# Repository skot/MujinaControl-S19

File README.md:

# MujinaControl-S19

An open-hardware Antminer S19 controlboard built around the Rockchip RV1106G2, for [Mujina](https://mujina.org) mining firmware. It keeps the bitcrane v3.1 form factor, outline, mounting holes and miner connectors, and replaces bitcrane's RP2040 with a Linux-capable SoC, Ethernet and local storage.

**Status (2026-11-14):** schematic complete, PCB placed and fully routed on six layers, with on-board WiFi. ERC 0; DRC 0 violations, 0 unconnected items, 0 schematic-parity issues. Every purchased part has a fab (LCSC) part number. Reviewed against the fab's manufacturing limits on 2026-11-14. **Not built or tested.** Read "Before ordering" below first.

Open `MujinaControl-S19.kicad_pro` with **KiCad 10.99 or later**. The files use a newer format than KiCad 10.0 can read.

## Hardware

- **SoC:** RV1106G2 with 128 MB in-package DDR3L, 24 MHz crystal and RTC crystal.
- **Storage:** W25N02KVZEIR 2 Gbit (256 MB) SPI NAND on the quad-SPI bus, following the Luckfox Pico Pro/Max, plus a microSD socket. A bootable NAND takes precedence over microSD.
- **Network and USB:** 100BASE-TX through the SoC's internal PHY and an integrated MagJack with the latch tab on top (HanRun HR915340A). USB-C device port for recovery and console; VBUS is detection-only, so **12 V must be present for USB recovery**.
- **Power:** 12 V from J1's 6-pin input (pins 1–3 positive, 4–6 ground) through reverse-polarity P-MOSFET Q1 (SiSS27DN-T1-GE3) and an SMBJ15A TVS. There is no controller fuse. Six TPS62933 bucks: 12 V → 5 V system (2 A budget), then sequenced 0.9 V core, 0.9 V CPU, 1.35 V DDR, 1.8 V and 3.3 V. Five TPS3808 supervisors (trip at about 90 % of each rail) qualify the sequence and hold reset.
- **Hashboards:** three ports, each with its own hardware UART, sharing one hashboard I²C bus; BCB100-style I²C/UART pull-ups and plug-detect pull-downs, and a TPS22919 switched 3.3 V supply per port, enabled directly by SoC GPIOs.
- **Fans:** four independent channels, PWM and tach, each sized for 3 A; the input stage carries all four fans plus the board. Each channel has both a 1×4 2.54 mm and a 2×2 4.2 mm footprint. The fab fits neither: solder in the one the machine needs. Two 100 µF bulk capacitors on the fan rail.
- **WiFi:** AMPAK AP6212 2.4 GHz 802.11 b/g/n module on 4-bit SDIO, with its own 26 MHz crystal and a U.FL connector (J19) for an external antenna; there is no on-board antenna. Bluetooth is not wired. See `docs/onboard-wifi.md`.
- **PSU and accessories:** PSU I²C and enable, 2×7 accessory header J15 (display I²C, six GPIO, 5 V / 3.3 V / 1.8 V; not fitted by the fab), console UART on J16 (pin 1 TX, 2 GND, 3 RX, 3.3 V), RESET and BOOT (maskrom) right-angle buttons beside the Ethernet jack.

J1–J14 keep bitcrane's pin assignments. For firmware, `docs/firmware-pins.md` lists every SoC pin, its function, polarity and voltage, with device-tree starting points. The history of the pin allocation is in `docs/pin-allocation.md`.

## Schematic

Eleven sheets: system overview, SoC interfaces, sequenced regulators, power qualification, SoC supply and bypass, boot storage and clocks, Ethernet and USB, hashboard interfaces, fan interfaces, input power and service, on-board WiFi. Cross-sheet signals use global labels; resistors use US-style symbols.

## PCB

- 110 × 100 mm, six layers, nominal 1.6 mm FR-4, ENIG, 1 oz outer / 0.5 oz inner, using the fab's JLC06161H-3313 stackup (`docs/pcb-stackup.md`).
- Layers: F.Cu signals and parts; In1 ground; In2 3.3 V plane with islands for core, DDR, 1.8 V, 5 V and 12 V; In3 slow signals; In4 ground; B.Cu signals.
- 330 footprints (including three fiducials and five chassis mounting pads), 2236 tracks, 852 vias. All vias are 0.45 mm diameter / 0.30 mm drill; minimum track 0.127 mm (SoC escapes and Ethernet pairs). About 380 vias sit in pads and need the fab's epoxy-filled, copper-capped via process.
- USB, Ethernet, SD card and SPI NAND are length-matched within the RV1106 hardware-guide limits. The WiFi SDIO lines are 49–60 mm with two layer changes each; the antenna line is 0.18 mm wide (50 Ω) on the top layer.
- Each regulator follows the TPS62933 datasheet layout, with its own stitched ground pour. 414 ground vias in total; wherever a via is allowed, no point is more than 6 mm from one.
- Exposed ground strips along the left and right edges, top and bottom, 3.7 mm wide from the outermost edge, for contact with the case slots (`docs/edge-ground-strips.md`).
- The Ethernet jack is a tab-up type and its face is 2.25 mm past the bottom board edge (`docs/ethernet-jack-position.md`).
- Reference designators are hidden on the silkscreen; the printed artwork is the RESET and BOOT labels and the Mujina badger logo.

Routing details, measurements and history are in `docs/routing-current.md`. The other routing documents describe the board before the 2026-11-10 rip-up.

## Assembly and parts

The board is meant to be assembled by the fab. Every purchased part carries `LCSC` and `MPN` fields: 295 placements per board in 68 part numbers, 26 basic, 9 preferred and 33 extended; the thin lines were checked against live stock on 2026-11-14. The RV1106G2 needs the fab's standard (not economic) assembly. Stock is low for the hashboard connectors J3–J5. See `docs/bom-fab-stock.md`. Fab settings and the instructions the order must carry are in `MujinaControl-S19.fab.json`.

## Before ordering

1. **Tell the fab.** The order must ask for epoxy-filled, copper-capped vias in pads, the controlled-impedance six-layer build-up with 0.0994 mm outer prepreg, and standard assembly. Check part rotations in the fab's placement preview. The routing was largely laid by a grid search: it is rule-clean but not tidy. The east-side hashboard lines and the fan and WiFi control lines are long with up to 9 vias. They are slow signals, but could be shortened.
2. **Hashboard and PSU compatibility.** Confirm the real S19 hashboard and PSU voltages, reset and plug-detect polarity, PSU-enable polarity and powered/unpowered behaviour. Matching bitcrane's connections is not a measured compatibility test.
3. **Power.** Check cold start, slow ramp, brownout and shutdown on all rails, the supervisor thresholds, and regulator transient response. Measure Q1 and the 12 V copper at the full four-fan load: Q1 (SiSS27DN, about 1.6 W hot at 14 A) has a thin, unmeasured thermal margin, see `docs/q1-upgrade.md`. Upstream wiring must protect against shorts, as there is no controller fuse.
4. **Footprints and parts.** Audit the footprints against datasheets, especially the SoC and NAND exposed pads, MagJack, crystals, inductors and microSD. The AP6212 footprint is drawn from the datasheet and unbuilt, and the module's buck inductor and capacitor values (L211 / C323) come from a sibling module's reference schematic. Check J19 and the WiFi crystal against the case slots at the east edge. Re-check stock before ordering.
5. **Firmware.** Bring up the UART, PWM and I²C pin groups, fan tach, hashboard power GPIOs, NAND boot, USB recovery and WiFi (SDIO in mux M1, `brcmfmac`, 32 kHz clock output) in the BSP. Keep the CPU at its fixed 0.9 V operating point.
6. **On hardware.** Tune the crystals; check USB and Ethernet signal integrity, ESD, thermals and EMC.

## Files

- `MujinaControl-S19.kicad_pro` with eleven `.kicad_sch` sheets, `.kicad_pcb` and `.kicad_dru` (custom rules).
- `lib/`, `models/`, `3d/`: project-local symbols, footprints and 3D models.
- `docs/`: design notes for each change (stackup, placement, regulators, routing, parts).
- `scripts/`: the original generator `build_schematic.py`. **Do not rerun it**; it would overwrite the hand-edited schematic. `validate_design.py` and `verify_readability.py` are read-only checks.
- `tools/export_fab.sh` writes the Gerbers, drill files, parts list and placement file for the fab into `mfg/MujinaControl-S19/` at the workspace root; `tools/fab_placement.csv` holds the placement corrections for the fab's part library (`docs/manufacturing-files.md`). `tools/render.sh` makes the picture above.
- Check reports, renders and working evidence are kept outside this repository, in `build/MujinaControl-S19/` at the workspace root.

## Sources and attribution

- [Braiins BCB100](https://github.com/braiins/BCB100): open-source S19 control board (CERN-OHL-S v2), used as the reference for hashboard interface biasing and logic-power control (I2C/UART pull-ups, plug-detect pull-downs and per-port switched 3.3 V). Thanks to Braiins for publishing it.
- [bitcrane](https://github.com/skot/bitcrane) v3.1 (CERN-OHL v2): form factor, outline, mounting holes, connector pinouts and placements, fan-header options, and the inherited `bitaxe` and `bitcrane` libraries.
- [Raven1106](https://github.com/EPSILON0-dev/Raven1106) v1.1: starting RV1106 package-pin definition, QFN footprint and model, and storage reference. Its full SBC circuit was not copied. No top-level licence was found for Raven; clarify reuse terms for the derived library assets before publishing them more widely.
- [Luckfox Pico Pro/Max](https://wiki.luckfox.com/Luckfox-Pico-RV1106/Downloads/): SPI NAND reference.
- Rockchip RV1106 datasheet Rev 2.2 and hardware design guide: pin functions, power and layout rules.
- [TI TPS62933](https://www.ti.com/lit/ds/symlink/tps62933.pdf), [TI TPS3808](https://www.ti.com/lit/ds/symlink/tps3808.pdf), [TI TPS22919](https://www.ti.com/lit/ds/symlink/tps22919.pdf), [Vishay SiSS27DN](https://www.vishay.com/docs/62847/siss27dn.pdf), [onsemi NTTFS008P03P8Z](https://www.onsemi.com/download/data-sheet/pdf/nttfs008p03p8z-d.pdf) and [Nexperia PESD3V3Y1BSF](https://assets.nexperia.com/documents/data-sheet/PESD3V3Y1BSF.pdf) datasheets.

Standard KiCad symbols and footprints are copied into the project-local libraries. Their original licence and attribution markings still apply.

## License

CERN Open Hardware Licence v2, Strongly Reciprocal (`LICENSE`).

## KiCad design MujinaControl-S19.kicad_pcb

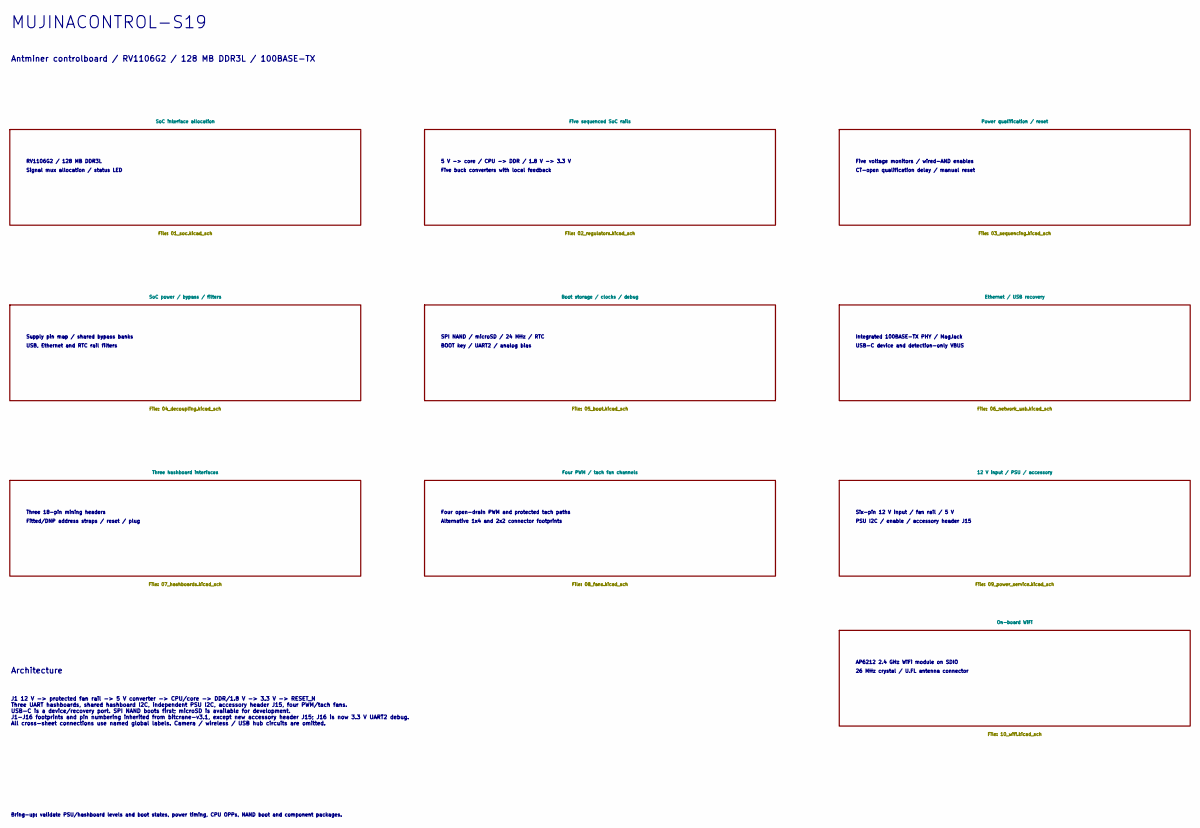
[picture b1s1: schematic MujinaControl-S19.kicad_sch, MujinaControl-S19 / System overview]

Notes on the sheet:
USB, Ethernet and RTC rail filters
Integrated 100BASE-TX PHY / MagJack
Five voltage monitors / wired-AND enables
PSU I2C / enable / accessory header J15
MUJINACONTROL-S19
5 V -> core / CPU -> DDR / 1.8 V -> 3.3 V
Architecture
Five buck converters with local feedback
BOOT key / UART2 / analog bias
Alternative 1x4 and 2x2 connector footprints
USB-C device and detection-only VBUS
SPI NAND / microSD / 24 MHz / RTC
J1 12 V -> protected fan rail -> 5 V converter -> CPU/core -> DDR/1.8 V -> 3.3 V -> RESET_N Three UART hashboards, shared hashboard I2C, independent PSU I2C, accessory header J15, four PWM/tach fans. USB-C is a device/recovery port. SPI NAND boots first; microSD is available for development. J1-J16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
Supply pin map / shared bypass banks
Antminer controlboard / RV1106G2 / 128 MB DDR3L / 100BASE-TX
CT-open qualification delay / manual reset
Fitted/DNP address straps / reset / plug
AP6212 2.4 GHz WiFi module on SDIO
RV1106G2 / 128 MB DDR3L
Bring-up: validate PSU/hashboard levels and boot states, power timing, CPU OPPs, NAND boot and component packages.
Signal mux allocation / status LED
Three 18-pin mining headers
26 MHz crystal / U.FL antenna connector
Four open-drain PWM and protected tach paths
Six-pin 12 V input / fan rail / 5 V

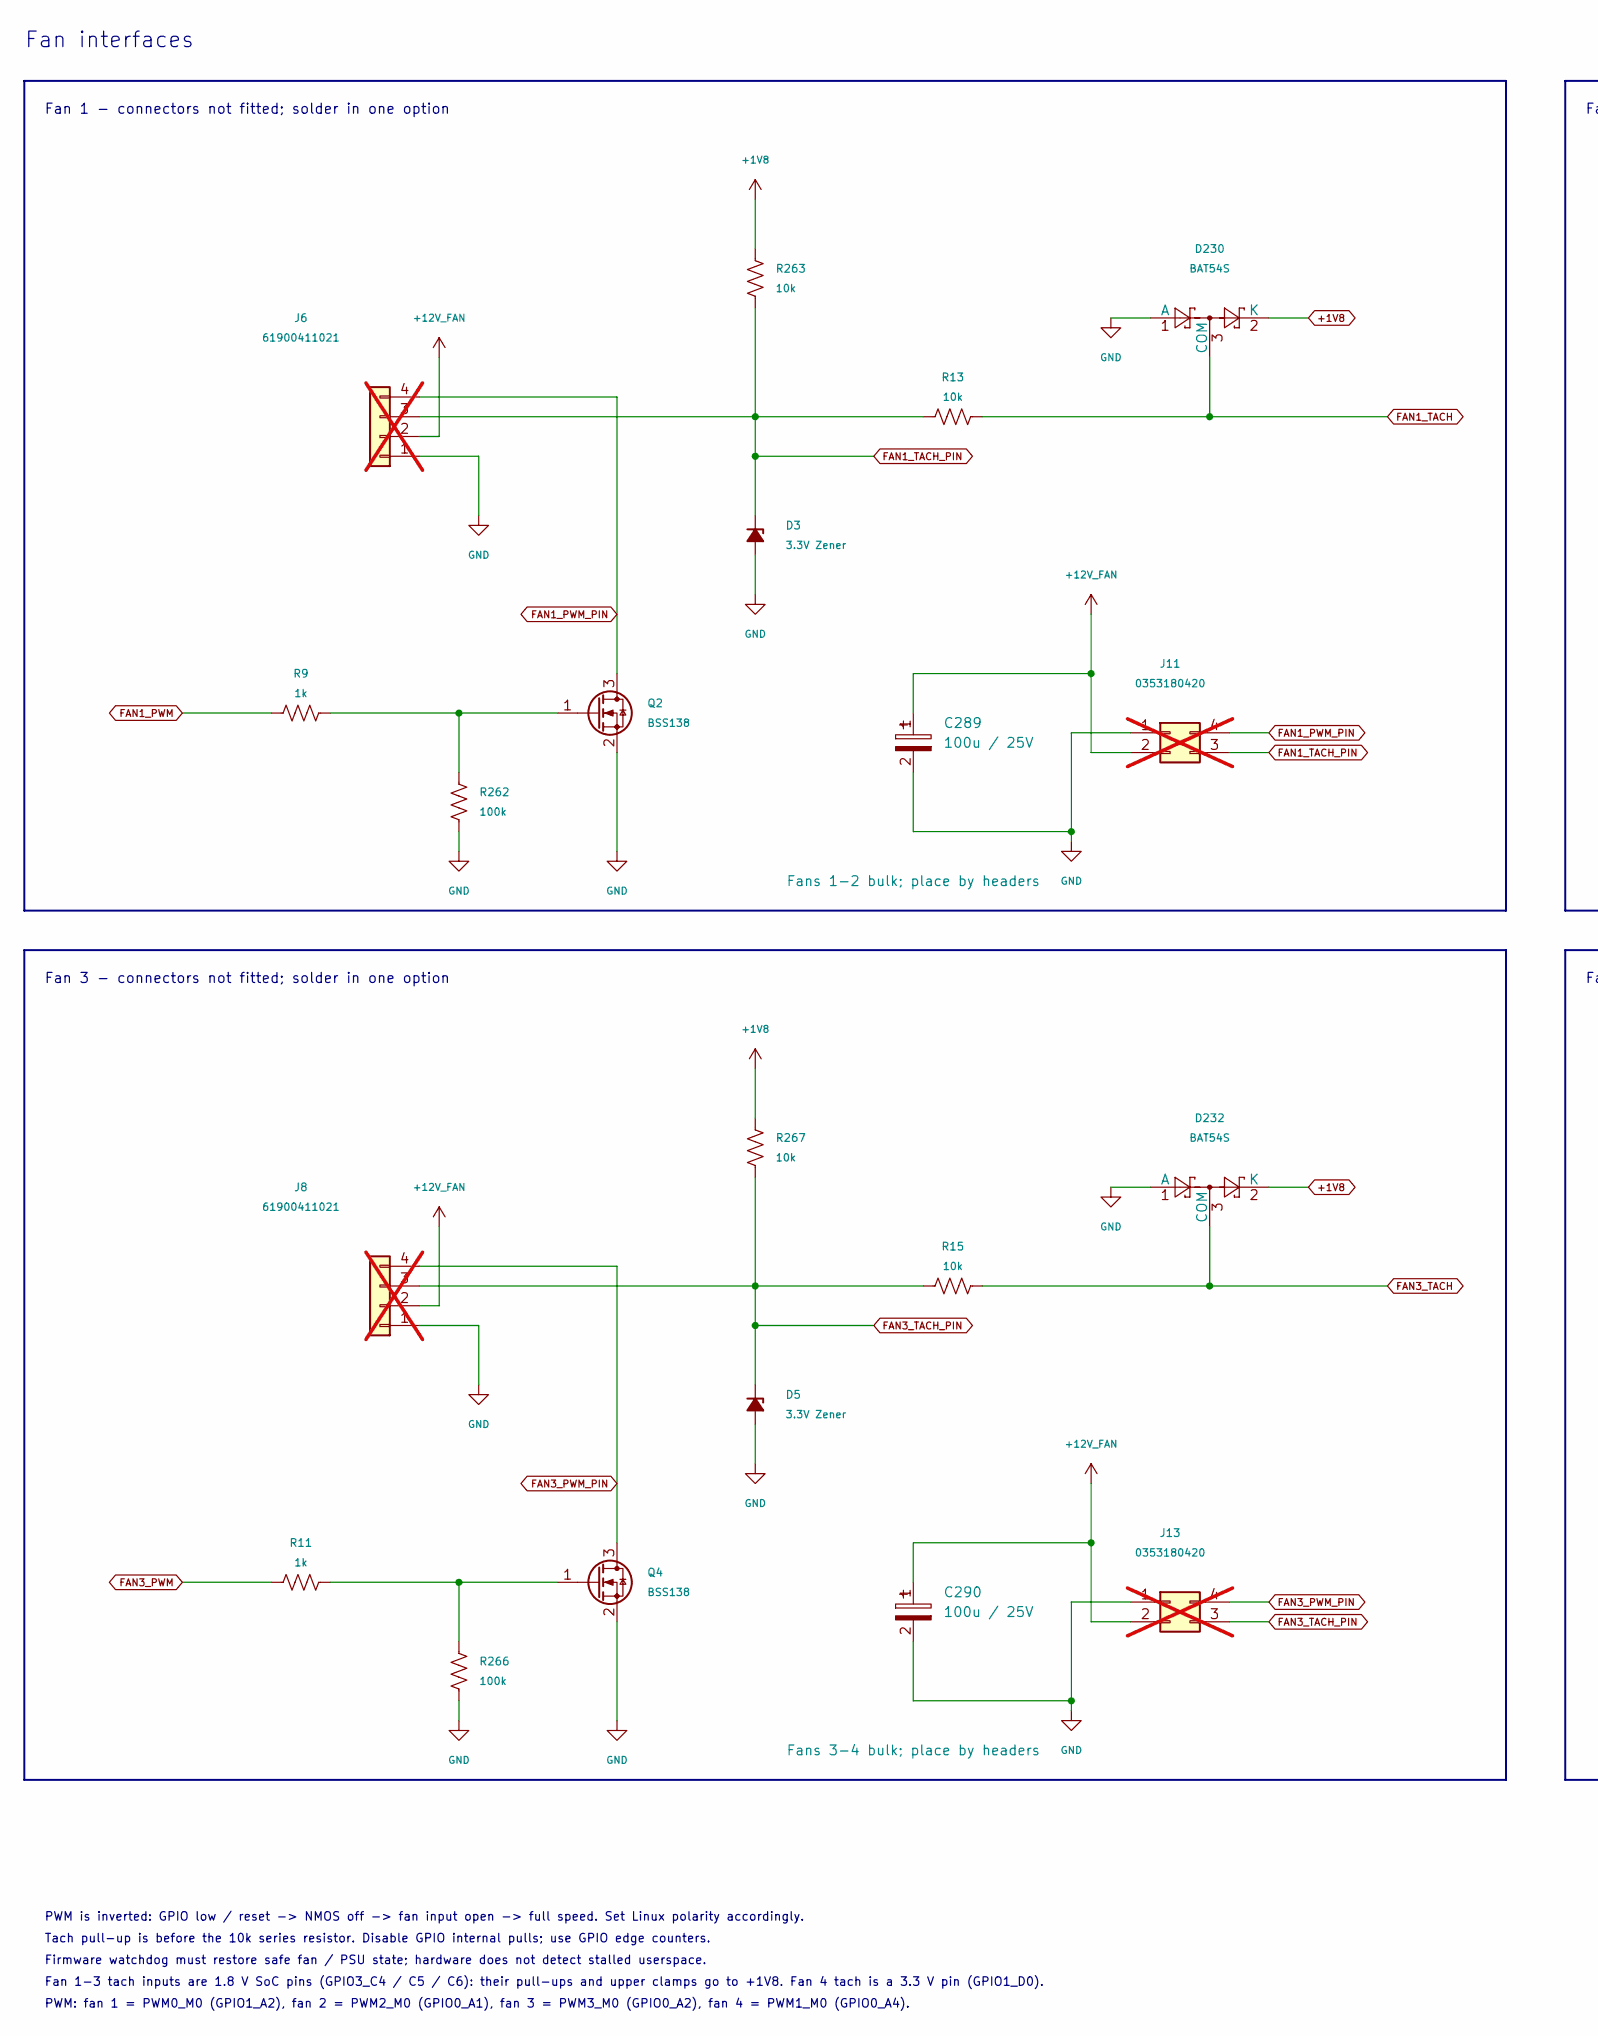
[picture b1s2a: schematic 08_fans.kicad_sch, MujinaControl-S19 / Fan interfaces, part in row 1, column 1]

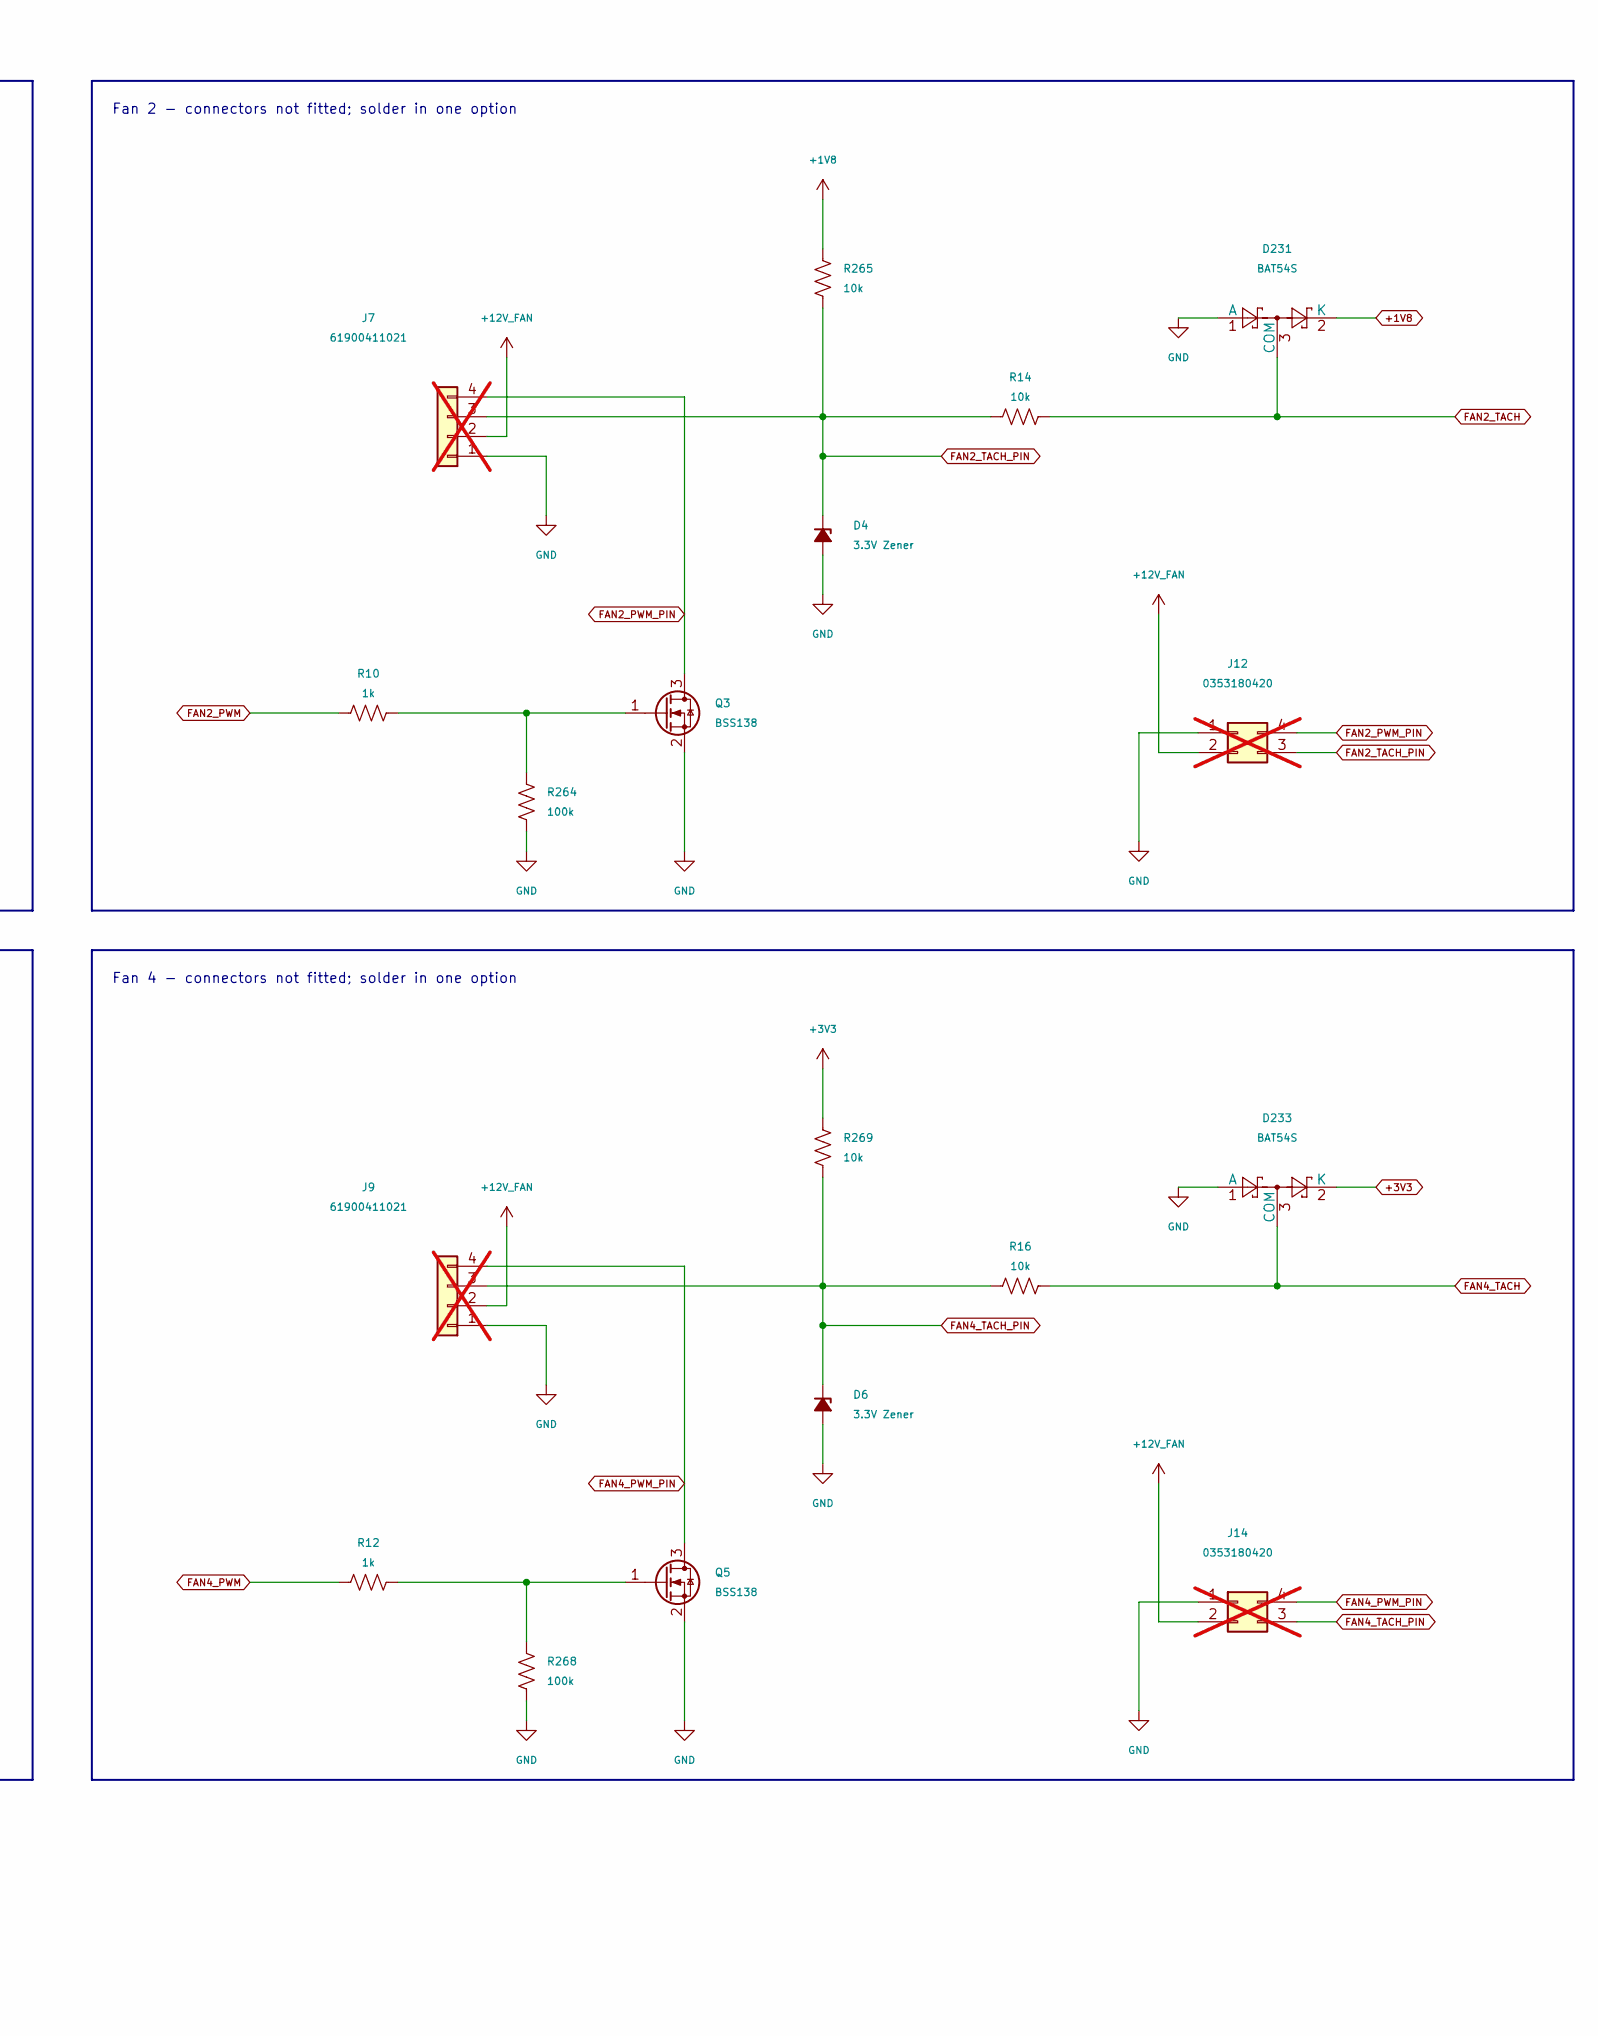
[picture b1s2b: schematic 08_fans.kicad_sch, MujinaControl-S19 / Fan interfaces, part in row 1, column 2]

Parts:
C289, C290: 100u / 25V; CP_Elec_6.3x7.7; MPN EEHZC1E101XP; LCSC C178640
D3, D4, D5, D6: 3.3V Zener; D_SOD-123; MPN BZT52C3V3; LCSC C19077396
D230, D231, D232, D233: BAT54S; SOT-23; MPN BAT54S; LCSC C7420333
J6, J7, J8, J9: 61900411021; CONN-TH_4P-P2.54_HCTL_HC-2510-4AW; MPN HC-2510-4AW; LCSC C2982043; not fitted
J11, J12, J13, J14: 0353180420; CONN-TH_4P-P4.20_5557-2X2AW; MPN 4.2-2*2AW; LCSC C54909; not fitted
Q2, Q3, Q4, Q5: BSS138; SOT-23; MPN BSS138; LCSC C7420339
R9, R10, R11, R12: 1k; R_0402_1005Metric; MPN 0402WGF1001TCE; LCSC C11702
R13, R14, R15, R16, R263, R265, R267, R269: 10k; R_0402_1005Metric; MPN 0402WGF1002TCE; LCSC C25744
R262, R264, R266, R268: 100k; R_0402_1005Metric; MPN 0402WGF1003TCE; LCSC C25741

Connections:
+1V8: D230.2 (K), D231.2 (K), D232.2 (K), R263.1, R265.1, R267.1; also elsewhere on the board
+3V3: D233.2 (K), R269.1; also elsewhere on the board
+12V_FAN: C289.1, C290.1, J6.2, J7.2, J8.2, J9.2, J11.2, J12.2, J13.2, J14.2; also elsewhere on the board
FAN1_PWM: R9.1; also elsewhere on the board
FAN1_PWM_PIN: J6.4, J11.4, Q2.3 (D)
FAN1_TACH: D230.3 (COM), R13.2; also elsewhere on the board
FAN1_TACH_PIN: D3.1 (K), J6.3, J11.3, R13.1, R263.2
FAN2_PWM: R10.1; also elsewhere on the board
FAN2_PWM_PIN: J7.4, J12.4, Q3.3 (D)
FAN2_TACH: D231.3 (COM), R14.2; also elsewhere on the board
FAN2_TACH_PIN: D4.1 (K), J7.3, J12.3, R14.1, R265.2
FAN3_PWM: R11.1; also elsewhere on the board
FAN3_PWM_PIN: J8.4, J13.4, Q4.3 (D)
FAN3_TACH: D232.3 (COM), R15.2; also elsewhere on the board
FAN3_TACH_PIN: D5.1 (K), J8.3, J13.3, R15.1, R267.2
FAN4_PWM: R12.1; also elsewhere on the board
FAN4_PWM_PIN: J9.4, J14.4, Q5.3 (D)
FAN4_TACH: D233.3 (COM), R16.2; also elsewhere on the board
FAN4_TACH_PIN: D6.1 (K), J9.3, J14.3, R16.1, R269.2
GND: C289.2, C290.2, D3.2 (A), D4.2 (A), D5.2 (A), D6.2 (A), D230.1 (A), D231.1 (A), D232.1 (A), D233.1 (A), J6.1, J7.1, J8.1, J9.1, J11.1, J12.1, J13.1, J14.1, Q2.2 (S), Q3.2 (S), Q4.2 (S), Q5.2 (S), R262.2, R264.2, R266.2, R268.2; also elsewhere on the board
unnamed: Q2.1 (G), R9.2, R262.1
unnamed: Q3.1 (G), R10.2, R264.1
unnamed: Q4.1 (G), R11.2, R266.1
unnamed: Q5.1 (G), R12.2, R268.1

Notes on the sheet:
Fan 4 - connectors not fitted; solder in one option
Fan 1-3 tach inputs are 1.8 V SoC pins (GPIO3_C4 / C5 / C6): their pull-ups and upper clamps go to +1V8. Fan 4 tach is a 3.3 V pin (GPIO1_D0).
Tach pull-up is before the 10k series resistor. Disable GPIO internal pulls; use GPIO edge counters.
Firmware watchdog must restore safe fan / PSU state; hardware does not detect stalled userspace.
PWM: fan 1 = PWM0_M0 (GPIO1_A2), fan 2 = PWM2_M0 (GPIO0_A1), fan 3 = PWM3_M0 (GPIO0_A2), fan 4 = PWM1_M0 (GPIO0_A4).
Fan interfaces
PWM is inverted: GPIO low / reset -> NMOS off -> fan input open -> full speed. Set Linux polarity accordingly.
Fan 2 - connectors not fitted; solder in one option
Fan 1 - connectors not fitted; solder in one option
Fan 3 - connectors not fitted; solder in one option

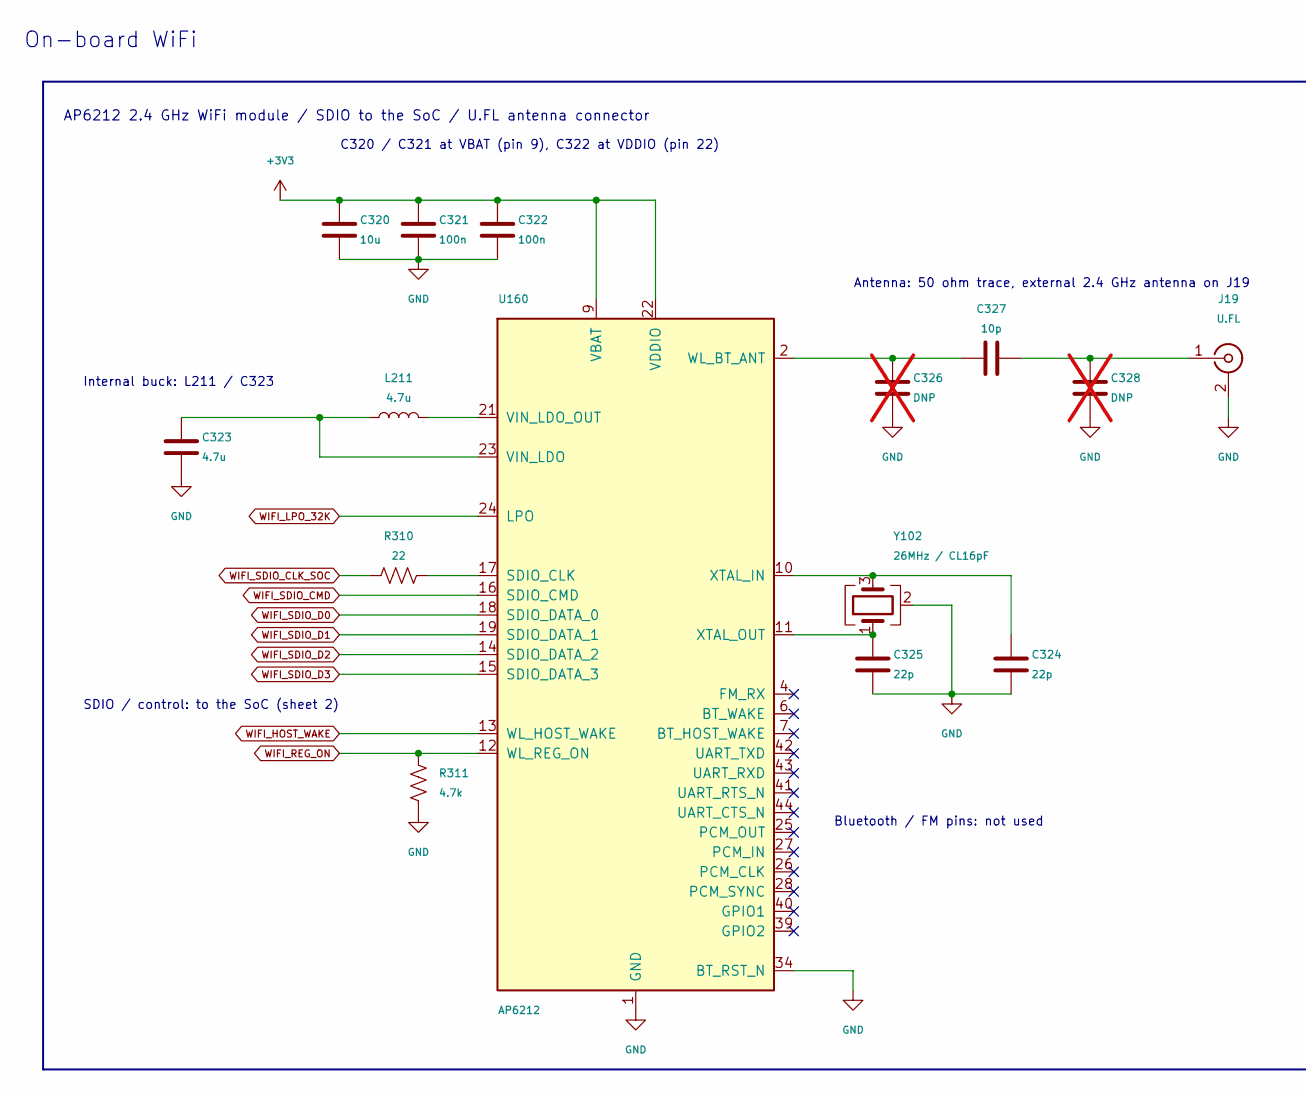
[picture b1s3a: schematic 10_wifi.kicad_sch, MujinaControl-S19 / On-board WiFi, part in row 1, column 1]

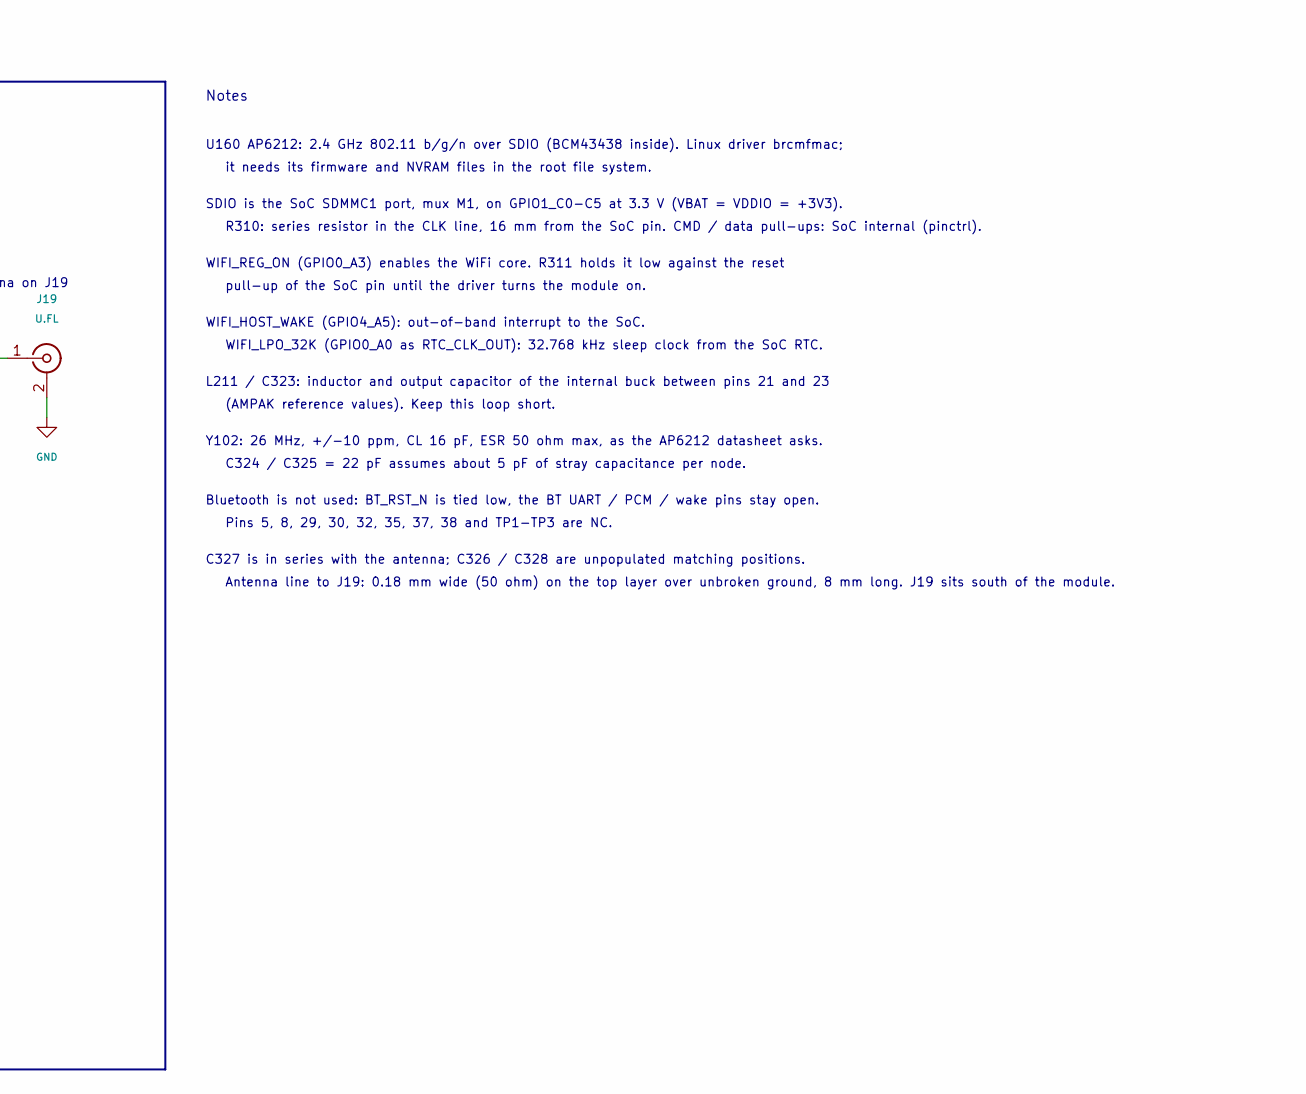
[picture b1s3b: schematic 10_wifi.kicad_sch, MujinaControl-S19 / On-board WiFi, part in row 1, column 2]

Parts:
C320: 10u; C_0805_2012Metric; MPN CL21A106KAYNNNE; LCSC C15850
C321, C322: 100n; C_0402_1005Metric; MPN CL05B104KO5NNNC; LCSC C1525
C323: 4.7u; C_0805_2012Metric; MPN CL21A475KAQNNNE; LCSC C1779
C324, C325: 22p; C_0402_1005Metric; MPN 0402CG220J500NT; LCSC C1555
C326, C328: DNP; C_0402_1005Metric; not fitted
C327: 10p; C_0402_1005Metric; MPN CL05C100JB5NNNC; LCSC C32949
J19: U.FL; U.FL_Hirose_U.FL-R-SMT-1_Vertical; MPN U.FL-R-SMT-1(80); LCSC C88374
L211: 4.7u; IND-SMD_L2.0-W1.6; MPN FTC201610S4R7MBCA; LCSC C5832346
R310: 22; R_0402_1005Metric; MPN 0402WGF220JTCE; LCSC C25092
R311: 4.7k; R_0402_1005Metric; MPN 0402WGF4701TCE; LCSC C25900
U160: AP6212; AMPAK_AP6212; MPN AP6212; LCSC C2798300
Y102: 26MHz / CL16pF; Crystal_SMD_3225-4Pin_3.2x2.5mm; MPN XL2EL89CQI-111YLC-26M; LCSC C19711727

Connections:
+3V3: C320.1, C321.1, C322.1, U160.9 (VBAT), U160.22 (VDDIO); also elsewhere on the board
GND: C320.2, C321.2, C322.2, C323.2, C324.2, C325.2, C326.2, C328.2, J19.2 (Ext), R311.2, U160.1 (GND), U160.3 (GND), U160.20 (GND), U160.31 (GND), U160.33 (GND), U160.34 (BT_RST_N), U160.36 (GND), Y102.2 (G), Y102.4 (G); also elsewhere on the board
unnamed: C327.1, C328.1, J19.1 (In)
unnamed: R310.1, U160.17 (SDIO_CLK)
unnamed: C323.1, L211.1, U160.23 (VIN_LDO)
unnamed: L211.2, U160.21 (VIN_LDO_OUT)
unnamed: C326.1, C327.2, U160.2 (WL_BT_ANT)
unnamed: C324.1, U160.10 (XTAL_IN), Y102.3
unnamed: C325.1, U160.11 (XTAL_OUT), Y102.1
WIFI_HOST_WAKE: U160.13 (WL_HOST_WAKE); also elsewhere on the board
WIFI_LPO_32K: U160.24 (LPO); also elsewhere on the board
WIFI_REG_ON: R311.1, U160.12 (WL_REG_ON); also elsewhere on the board
WIFI_SDIO_CLK_SOC: R310.2; also elsewhere on the board
WIFI_SDIO_CMD: U160.16 (SDIO_CMD); also elsewhere on the board
WIFI_SDIO_D0: U160.18 (SDIO_DATA_0); also elsewhere on the board
WIFI_SDIO_D1: U160.19 (SDIO_DATA_1); also elsewhere on the board
WIFI_SDIO_D2: U160.14 (SDIO_DATA_2); also elsewhere on the board
WIFI_SDIO_D3: U160.15 (SDIO_DATA_3); also elsewhere on the board

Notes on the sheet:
AP6212 2.4 GHz WiFi module / SDIO to the SoC / U.FL antenna connector
Pins 5, 8, 29, 30, 32, 35, 37, 38 and TP1-TP3 are NC.
WIFI_REG_ON (GPIO0_A3) enables the WiFi core. R311 holds it low against the reset
(AMPAK reference values). Keep this loop short.
Antenna: 50 ohm trace, external 2.4 GHz antenna on J19
On-board WiFi
SDIO is the SoC SDMMC1 port, mux M1, on GPIO1_C0-C5 at 3.3 V (VBAT = VDDIO = +3V3).
C320 / C321 at VBAT (pin 9), C322 at VDDIO (pin 22)
U160 AP6212: 2.4 GHz 802.11 b/g/n over SDIO (BCM43438 inside). Linux driver brcmfmac;
WIFI_HOST_WAKE (GPIO4_A5): out-of-band interrupt to the SoC.
it needs its firmware and NVRAM files in the root file system.
C327 is in series with the antenna; C326 / C328 are unpopulated matching positions.
Antenna line to J19: 0.18 mm wide (50 ohm) on the top layer over unbroken ground, 8 mm long. J19 sits south of the module.
R310: series resistor in the CLK line, 16 mm from the SoC pin. CMD / data pull-ups: SoC internal (pinctrl).
Y102: 26 MHz, +/-10 ppm, CL 16 pF, ESR 50 ohm max, as the AP6212 datasheet asks.
Notes
SDIO / control: to the SoC (sheet 2)
Internal buck: L211 / C323
Bluetooth / FM pins: not used
Bluetooth is not used: BT_RST_N is tied low, the BT UART / PCM / wake pins stay open.
L211 / C323: inductor and output capacitor of the internal buck between pins 21 and 23
C324 / C325 = 22 pF assumes about 5 pF of stray capacitance per node.
pull-up of the SoC pin until the driver turns the module on.
WIFI_LPO_32K (GPIO0_A0 as RTC_CLK_OUT): 32.768 kHz sleep clock from the SoC RTC.
